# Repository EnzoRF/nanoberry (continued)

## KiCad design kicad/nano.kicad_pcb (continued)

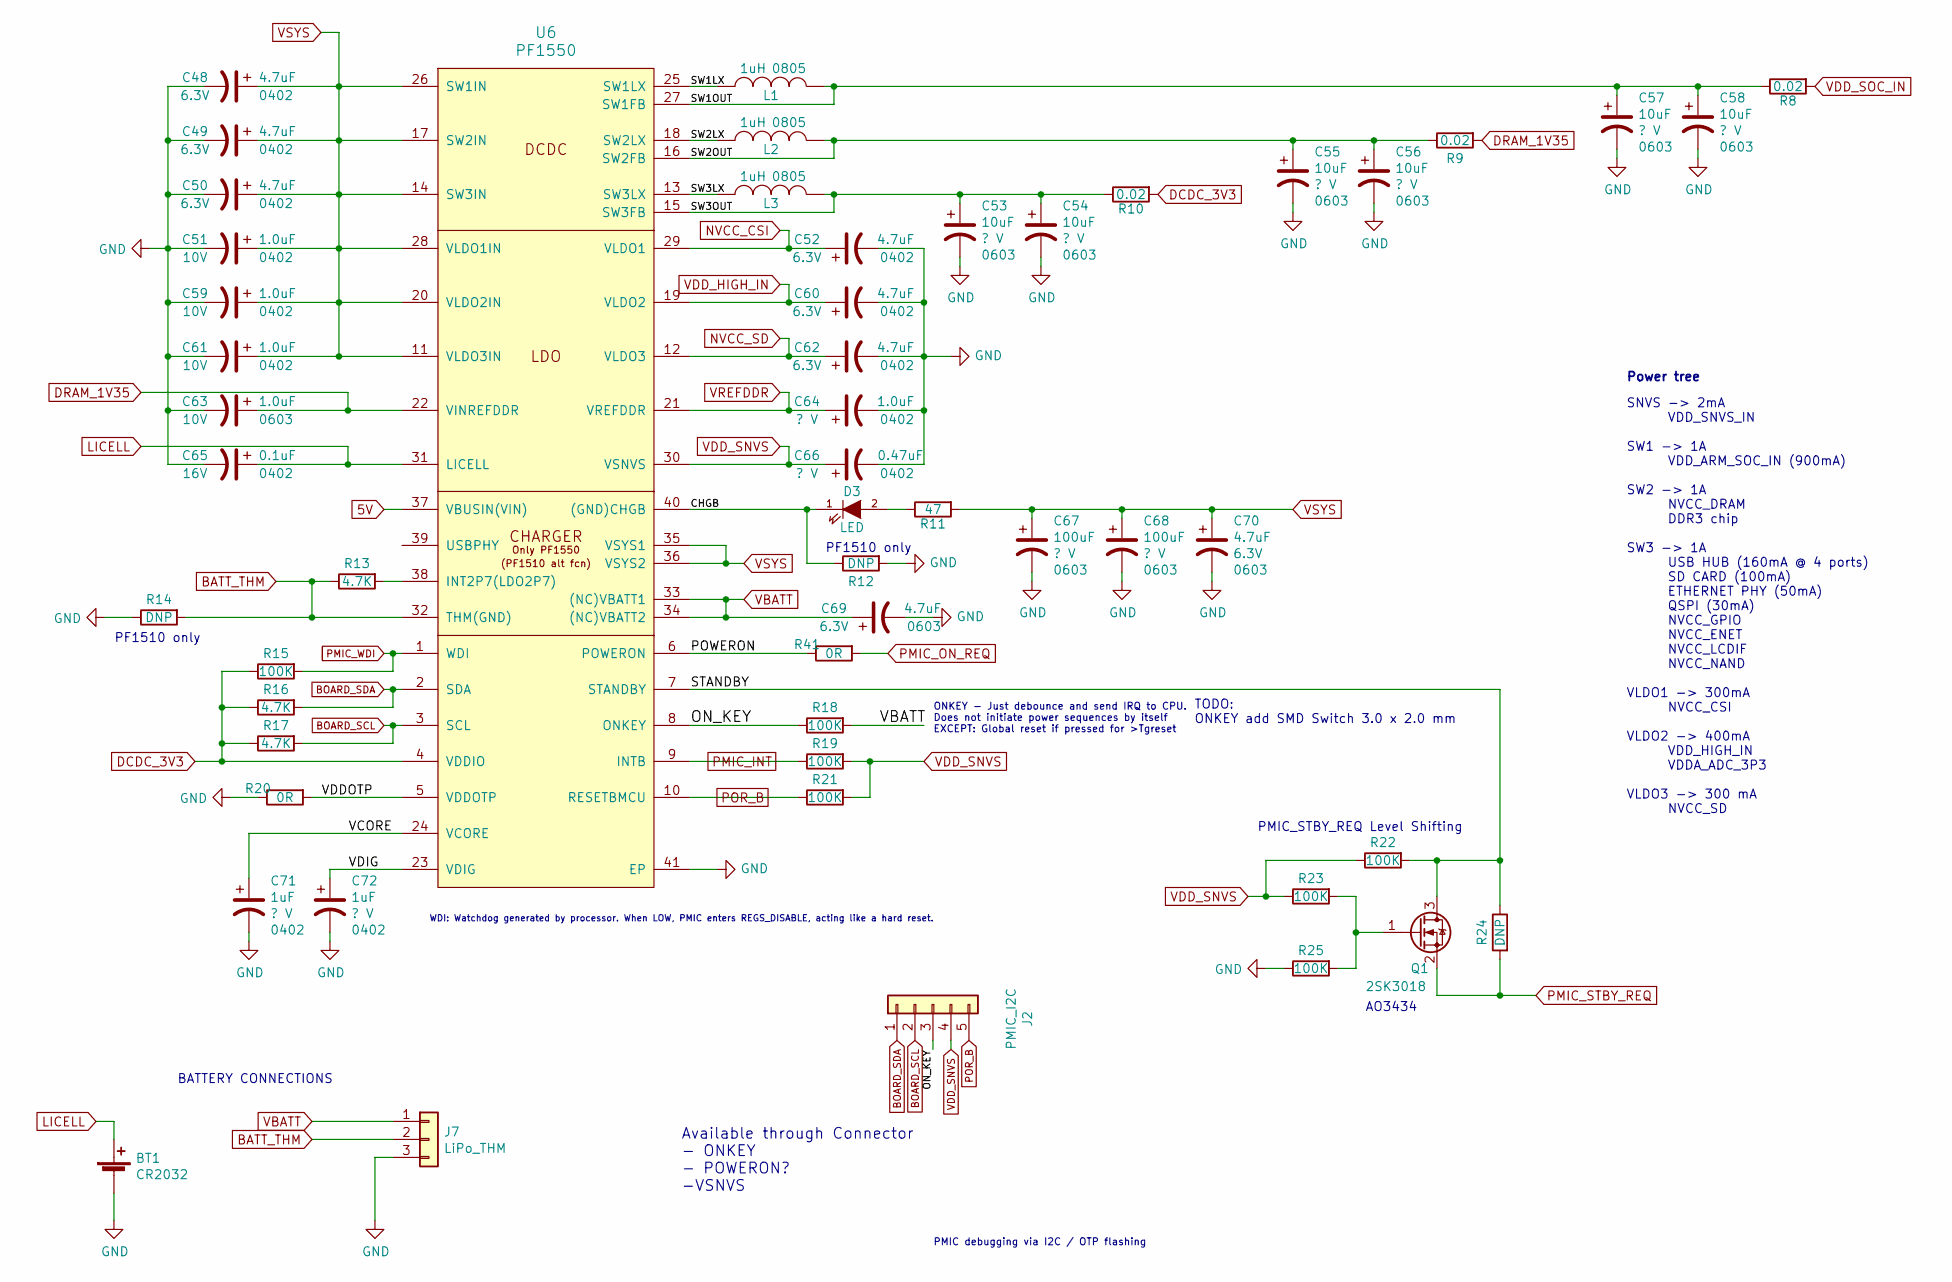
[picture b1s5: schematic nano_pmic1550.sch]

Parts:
BT1: CR2032; BatteryHolder_Keystone_1058_1x2032
C48, C49, C50, C52, C60, C62: 4.7uF; C_0402_narrow; Voltage 6.3V
C51, C59, C61: 1.0uF; C_0402_narrow; Voltage 10V
C53, C54, C55, C56, C57, C58: 10uF; C_0603_narrow; Voltage ? V
C63: 1.0uF; C_0603_narrow; Voltage 10V
C64: 1.0uF; C_0402_narrow; Voltage ? V
C65: 0.1uF; C_0603_narrow; Voltage 16V
C66: 0.47uF; C_0402_narrow; Voltage ? V
C67, C68: 100uF; C_0603_narrow; Voltage ? V
C69, C70: 4.7uF; C_0603_narrow; Voltage 6.3V
C71, C72: 1uF; C_0402_narrow; Voltage ? V
D3: LED; LED_0402_1005Metric
J2: PMIC_I2C; PinHeader_1x05_P2.54mm_Vertical
J7: LiPo_THM; PinHeader_1x03_P2.54mm_Vertical
L1, L2, L3: 1uH; L_0805_narrow
Q1: 2SK3018; SOT-23
R8, R9, R10: 0.02; R_0402_narrow
R11: 47; R_0402_narrow
R12, R14, R24: DNP; R_0402_narrow
R13, R16, R17: 4.7K; R_0402_narrow
R15, R18, R19, R21, R22, R23, R25: 100K; R_0402_narrow
R20, R41: 0R; R_0402_narrow
U6: PF1550; QFN-40-1EP_5x5mm_P0.4mm_EP3.6x3.6mm_ThermalVias

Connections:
5V: U6.37 (VBUSIN(VIN)); also elsewhere on the board
/PMIC PF1550/CHGB: D3.1 (K), R12.1, U6.40 ((GND)CHGB)
/PMIC PF1550/ON_KEY: J2.3, R18.1, U6.8 (ONKEY)
/PMIC PF1550/POWERON: R41.1, U6.6 (POWERON)
/PMIC PF1550/STANDBY: Q1.3 (D), R22.2, R24.1, U6.7 (STANDBY)
/PMIC PF1550/SW1LX: L1.2, U6.25 (SW1LX)
/PMIC PF1550/SW1OUT: C57.1, C58.1, L1.1, R8.1, U6.27 (SW1FB)
/PMIC PF1550/SW2LX: L2.2, U6.18 (SW2LX)
/PMIC PF1550/SW2OUT: C55.1, C56.1, L2.1, R9.1, U6.16 (SW2FB)
/PMIC PF1550/SW3LX: L3.2, U6.13 (SW3LX)
/PMIC PF1550/SW3OUT: C53.1, C54.1, L3.1, R10.1, U6.15 (SW3FB)
/PMIC PF1550/VCORE: C71.1, U6.24 (VCORE)
/PMIC PF1550/VDDOTP: R20.2, U6.5 (VDDOTP)
/PMIC PF1550/VDIG: C72.1, U6.23 (VDIG)
BATT_THM: J7.2, R13.1, R14.2, U6.32 (THM(GND))
BOARD_SCL: J2.2, R17.2, U6.3 (SCL); also elsewhere on the board
BOARD_SDA: J2.1, R16.2, U6.2 (SDA); also elsewhere on the board
DCDC_3V3: R10.2, R15.1, R16.1, R17.1, U6.4 (VDDIO); also elsewhere on the board
DRAM_1V35: C63.1, R9.2, U6.22 (VINREFDDR); also elsewhere on the board
GND: BT1.2 (-), C48.2, C49.2, C50.2, C51.2, C52.2, C53.2, C54.2, C55.2, C56.2, C57.2, C58.2, C59.2, C60.2, C61.2, C62.2, C63.2, C64.2, C65.2, C66.2, C67.2, C68.2, C69.2, C70.2, C71.2, C72.2, J7.3, R12.2, R14.1, R20.1, R25.1, U6.41 (EP); also elsewhere on the board
LICELL: BT1.1 (+), C65.1, U6.31 (LICELL)
NVCC_CSI: C52.1, U6.29 (VLDO1); also elsewhere on the board
NVCC_SD: C62.1, U6.12 (VLDO3); also elsewhere on the board
unnamed: D3.2 (A), R11.1
unnamed: Q1.1 (G), R23.2, R25.2
unnamed: R13.2, U6.38 (INT2P7(LDO2P7))
PMIC_INT: R19.1, U6.9 (INTB); also elsewhere on the board
PMIC_ON_REQ: R41.2; also elsewhere on the board
PMIC_STBY_REQ: Q1.2 (S), R24.2; also elsewhere on the board
PMIC_WDI: R15.2, U6.1 (WDI); also elsewhere on the board
POR_B: J2.5, R21.1, U6.10 (RESETBMCU); also elsewhere on the board
VBATT: C69.1, J7.1, R18.2, U6.33 ((NC)VBATT1), U6.34 ((NC)VBATT2); also elsewhere on the board
VDD_HIGH_IN: C60.1, U6.19 (VLDO2); also elsewhere on the board
VDD_SNVS: C66.1, J2.4, R19.2, R21.2, R22.1, R23.1, U6.30 (VSNVS); also elsewhere on the board
VDD_SOC_IN: R8.2; also elsewhere on the board
VREFDDR: C64.1, U6.21 (VREFDDR); also elsewhere on the board
VSYS: C48.1, C49.1, C50.1, C51.1, C59.1, C61.1, C67.1, C68.1, C70.1, R11.2, U6.11 (VLDO3IN), U6.14 (SW3IN), U6.17 (SW2IN), U6.20 (VLDO2IN), U6.26 (SW1IN), U6.28 (VLDO1IN), U6.35 (VSYS1), U6.36 (VSYS2)

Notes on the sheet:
Available through Connector - ONKEY - POWERON? -VSNVS
Power tree
SNVS -> 2mA VDD_SNVS_IN SW1 -> 1A VDD_ARM_SOC_IN (900mA) SW2 -> 1A NVCC_DRAM DDR3 chip SW3 -> 1A USB HUB (160mA @ 4 ports) SD CARD (100mA) ETHERNET PHY (50mA) QSPI (30mA) NVCC_GPIO NVCC_ENET NVCC_LCDIF NVCC_NAND VLDO1 -> 300mA NVCC_CSI VLDO2 -> 400mA VDD_HIGH_IN VDDA_ADC_3P3 VLDO3 -> 300 mA NVCC_SD
PF1510 only
PMIC debugging via I2C / OTP flashing
ONKEY - Just debounce and send IRQ to CPU. Does not initiate power sequences by itself EXCEPT: Global reset if pressed for >Tgreset
PMIC_STBY_REQ Level Shifting
AO3434
BATTERY CONNECTIONS
WDI: Watchdog generated by processor. When LOW, PMIC enters REGS_DISABLE, acting like a hard reset.
TODO: ONKEY add SMD Switch 3.0 x 2.0 mm

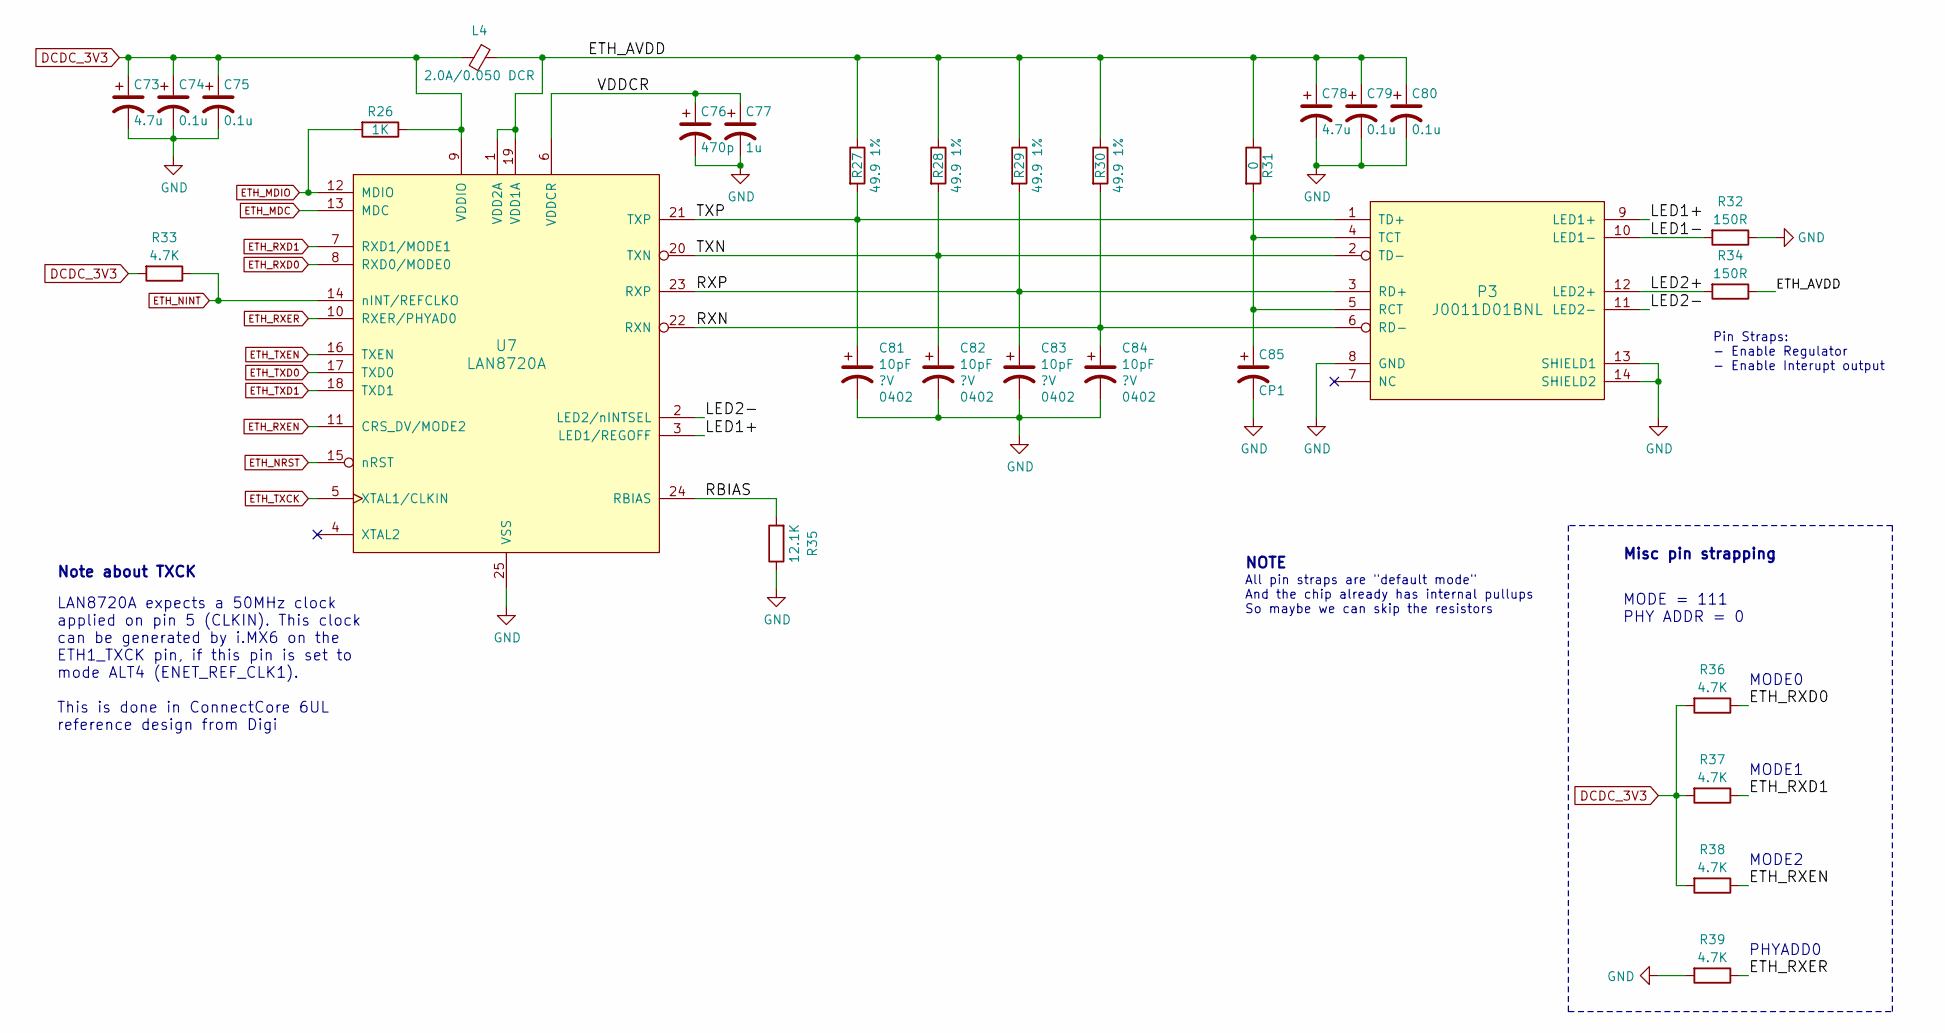
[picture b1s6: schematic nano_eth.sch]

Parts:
C73, C78: 4.7u; C_0603_narrow
C74, C75, C79, C80: 0.1u; C_0402_narrow
C76: 470p; C_0402_narrow
C77: 1u; C_0603_narrow
C81, C82, C83, C84: 10pF; C_0402_narrow; Voltage ?V
C85: CP1; C_0402_narrow
L4: 2.0A/0.050 DCR; R_0805_2012Metric
P3: J0011D01BNL; MTJ-88TX1-FSD-D1LH-M4Y
R26: 1K; R_0402_narrow
R27, R28, R29, R30: 49.9 1%; R_0402_narrow
R31: 0; R_0402_narrow
R32, R34: 150R; R_0402_narrow
R33, R36, R37, R38, R39: 4.7K; R_0402_narrow
R35: 12.1K; R_0402_narrow
U7: LAN8720A; QFN-24-1EP_4x4mm_P0.5mm_EP2.6x2.6mm_ThermalVias

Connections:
/ETHERNET/ETH_AVDD: C78.1, C79.1, C80.1, L4.1, R27.1, R28.1, R29.1, R30.1, R31.1, R34.1, U7.1 (VDD2A), U7.19 (VDD1A)
/ETHERNET/LED1+: P3.9 (LED1+), U7.3 (LED1/REGOFF)
/ETHERNET/LED1-: P3.10 (LED1-), R32.2
/ETHERNET/LED2+: P3.12 (LED2+), R34.2
/ETHERNET/LED2-: P3.11 (LED2-), U7.2 (LED2/nINTSEL)
/ETHERNET/RBIAS: R35.2, U7.24 (RBIAS)
/ETHERNET/RXN: C84.1, P3.6 (RD-), R30.2, U7.22 (RXN)
/ETHERNET/RXP: C83.1, P3.3 (RD+), R29.2, U7.23 (RXP)
/ETHERNET/TXN: C82.1, P3.2 (TD-), R28.2, U7.20 (TXN)
/ETHERNET/TXP: C81.1, P3.1 (TD+), R27.2, U7.21 (TXP)
/ETHERNET/VDDCR: C76.1, C77.1, U7.6 (VDDCR)
DCDC_3V3: C73.1, C74.1, C75.1, L4.2, R26.1, R33.2, R36.2, R37.2, R38.2, U7.9 (VDDIO); also elsewhere on the board
ETH_MDC: U7.13 (MDC); also elsewhere on the board
ETH_MDIO: R26.2, U7.12 (MDIO); also elsewhere on the board
ETH_NINT: R33.1, U7.14 (nINT/REFCLKO); also elsewhere on the board
ETH_NRST: U7.15 (nRST); also elsewhere on the board
ETH_RXD0: R36.1, U7.8 (RXD0/MODE0); also elsewhere on the board
ETH_RXD1: R37.1, U7.7 (RXD1/MODE1); also elsewhere on the board
ETH_RXEN: R38.1, U7.11 (CRS_DV/MODE2); also elsewhere on the board
ETH_RXER: R39.1, U7.10 (RXER/PHYAD0); also elsewhere on the board
ETH_TXCK: U7.5 (XTAL1/CLKIN); also elsewhere on the board
ETH_TXD0: U7.17 (TXD0); also elsewhere on the board
ETH_TXD1: U7.18 (TXD1); also elsewhere on the board
ETH_TXEN: U7.16 (TXEN); also elsewhere on the board
GND: C73.2, C74.2, C75.2, C76.2, C77.2, C78.2, C79.2, C80.2, C81.2, C82.2, C83.2, C84.2, C85.2, P3.8 (GND), P3.13 (SHIELD1), P3.14 (SHIELD2), R32.1, R35.1, R39.2, U7.25 (VSS); also elsewhere on the board
unnamed: C85.1, P3.4 (TCT), P3.5 (RCT), R31.2

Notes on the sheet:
Note about TXCK
LAN8720A expects a 50MHz clock applied on pin 5 (CLKIN). This clock can be generated by i.MX6 on the ETH1_TXCK pin, if this pin is set to mode ALT4 (ENET_REF_CLK1). This is done in ConnectCore 6UL reference design from Digi
PHYADD0
MODE0
MODE1
MODE2
MODE = 111 PHY ADDR = 0
Misc pin strapping
Pin Straps: - Enable Regulator - Enable Interupt output
NOTE
All pin straps are "default mode" And the chip already has internal pullups So maybe we can skip the resistors

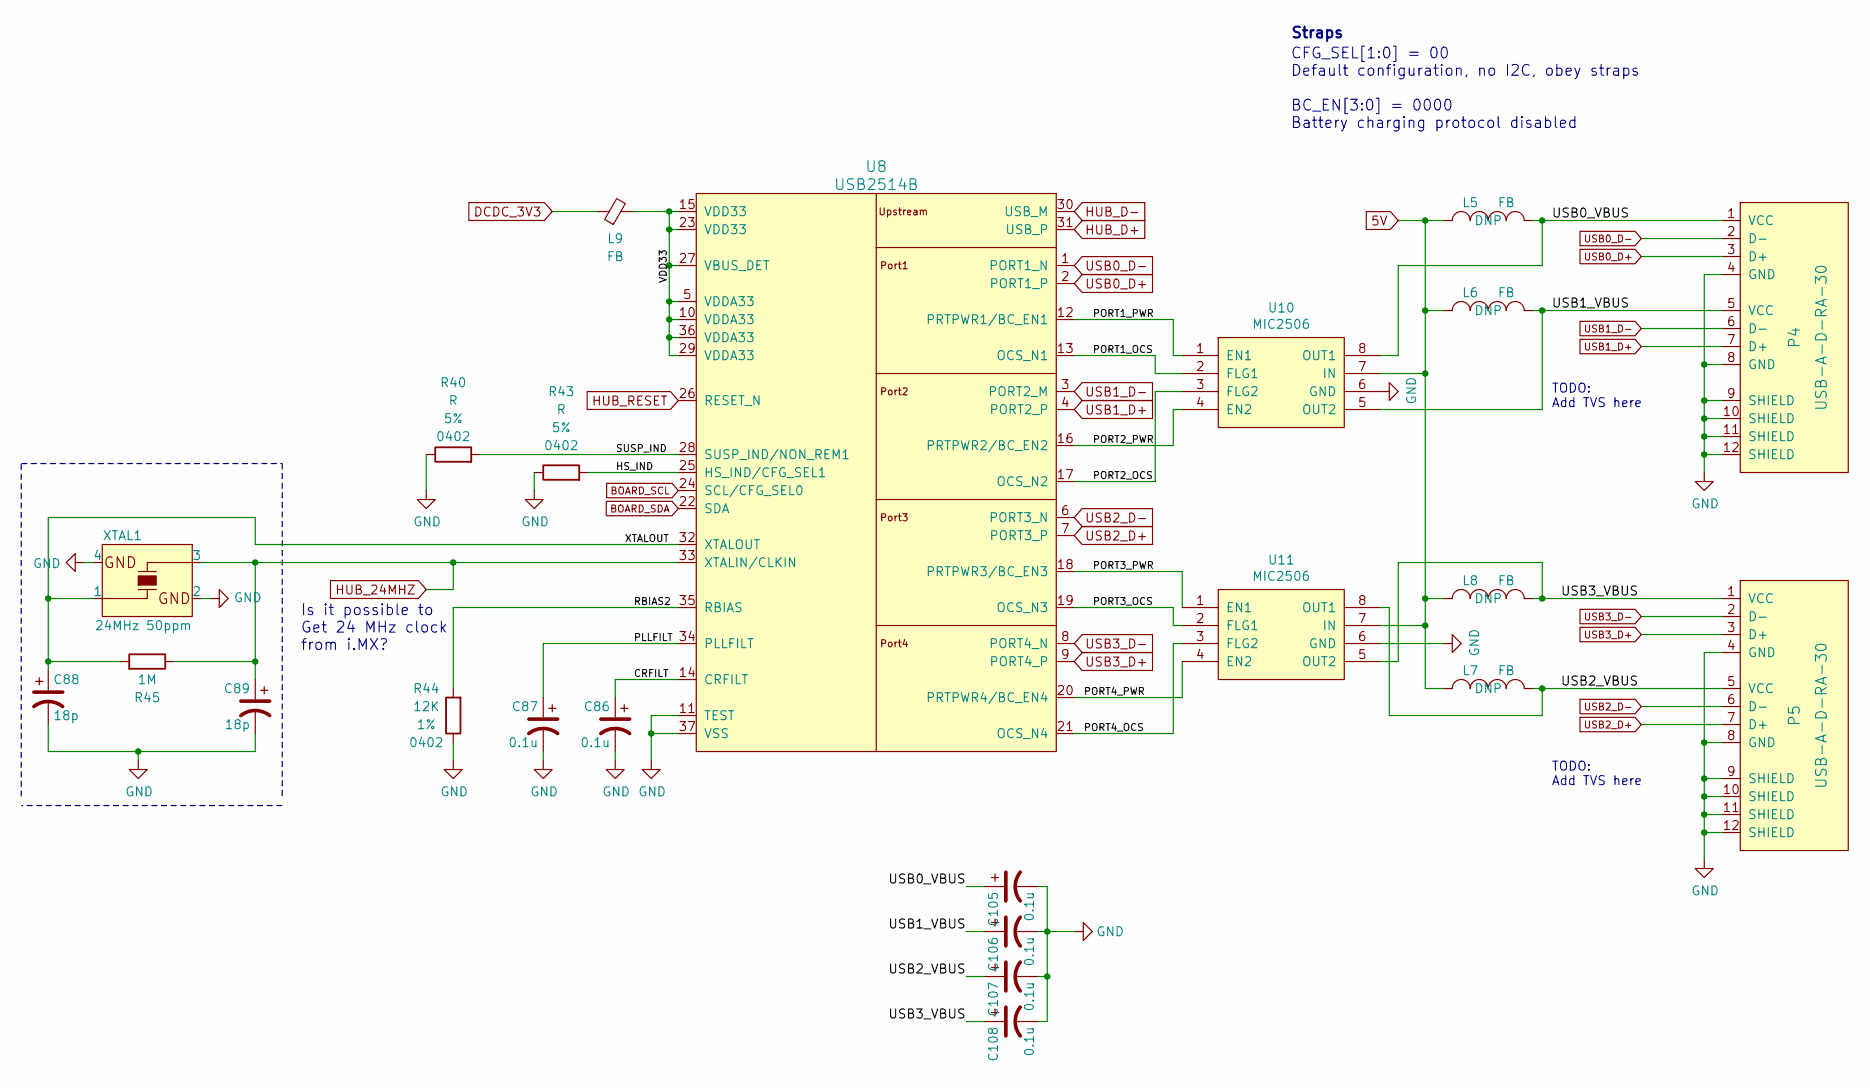
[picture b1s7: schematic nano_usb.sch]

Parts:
C86, C87, C105, C106, C107, C108: 0.1u; C_0402_narrow
C88, C89: 18p; C_0402_narrow
L5, L6, L7, L8, L9: FB; L_0805_narrow
P4, P5: USB-A-D-RA-30
R40, R43: R; R_0402_narrow; Tolerance 5%
R44: 12K; R_0402_narrow; Tolerance 1%
R45: 1M; R_0402_narrow
U8: USB2514B; QFN-36-1EP_6x6mm_P0.5mm_EP3.7x3.7mm_ThermalVias
U10, U11: MIC2506; SOIC-8_3.9x4.9mm_P1.27mm
XTAL1: 24MHz 50ppm; Oscillator_SMD_EuroQuartz_XO32-4Pin_3.2x2.5mm

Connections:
5V: L5.1, L6.1, L7.1, L8.1, U10.7 (IN), U11.7 (IN); also elsewhere on the board
/USB HUB/CRFILT: C86.1, U8.14 (CRFILT)
/USB HUB/HS_IND: R43.2, U8.25 (HS_IND/CFG_SEL1)
/USB HUB/PLLFILT: C87.1, U8.34 (PLLFILT)
/USB HUB/PORT1_OCS: U8.13 (OCS_N1), U10.2 (FLG1)
/USB HUB/PORT1_PWR: U8.12 (PRTPWR1/BC_EN1), U10.1 (EN1)
/USB HUB/PORT2_OCS: U8.17 (OCS_N2), U10.3 (FLG2)
/USB HUB/PORT2_PWR: U8.16 (PRTPWR2/BC_EN2), U10.4 (EN2)
/USB HUB/PORT3_OCS: U8.19 (OCS_N3), U11.2 (FLG1)
/USB HUB/PORT3_PWR: U8.18 (PRTPWR3/BC_EN3), U11.1 (EN1)
/USB HUB/PORT4_OCS: U8.21 (OCS_N4), U11.3 (FLG2)
/USB HUB/PORT4_PWR: U8.20 (PRTPWR4/BC_EN4), U11.4 (EN2)
/USB HUB/RBIAS2: R44.2, U8.35 (RBIAS)
/USB HUB/SUSP_IND: R40.2, U8.28 (SUSP_IND/NON_REM1)
/USB HUB/USB0_VBUS: C105.1, L5.2, P4.1 (VCC), U10.8 (OUT1)
/USB HUB/USB1_VBUS: C106.1, L6.2, P4.5 (VCC), U10.5 (OUT2)
/USB HUB/USB2_VBUS: C107.1, L7.2, P5.5 (VCC), U11.8 (OUT1)
/USB HUB/USB3_VBUS: C108.1, L8.2, P5.1 (VCC), U11.5 (OUT2)
/USB HUB/VDD33: L9.2, U8.5 (VDDA33), U8.10 (VDDA33), U8.15 (VDD33), U8.23 (VDD33), U8.27 (VBUS_DET), U8.29 (VDDA33), U8.36 (VDDA33)
/USB HUB/XTALOUT: C88.1, R45.2, U8.32 (XTALOUT), XTAL1.1
BOARD_SCL: U8.24 (SCL/CFG_SEL0); also elsewhere on the board
BOARD_SDA: U8.22 (SDA); also elsewhere on the board
DCDC_3V3: L9.1; also elsewhere on the board
GND: C86.2, C87.2, C88.2, C89.2, C105.2, C106.2, C107.2, C108.2, P4.4 (GND), P4.8 (GND), P4.9 (SHIELD), P4.10 (SHIELD), P4.11 (SHIELD), P4.12 (SHIELD), P5.4 (GND), P5.8 (GND), P5.9 (SHIELD), P5.10 (SHIELD), P5.11 (SHIELD), P5.12 (SHIELD), R40.1, R43.1, R44.1, U8.11 (TEST), U8.37 (VSS), U10.6 (GND), U11.6 (GND), XTAL1.2, XTAL1.4; also elsewhere on the board
HUB_24MHZ: C89.1, R45.1, U8.33 (XTALIN/CLKIN), XTAL1.3; also elsewhere on the board
HUB_D+: U8.31 (USB_P); also elsewhere on the board
HUB_D-: U8.30 (USB_M); also elsewhere on the board
HUB_RESET: U8.26 (RESET_N); also elsewhere on the board
USB0_D+: P4.3 (D+), U8.2 (PORT1_P)
USB0_D-: P4.2 (D-), U8.1 (PORT1_N)
USB1_D+: P4.7 (D+), U8.4 (PORT2_P)
USB1_D-: P4.6 (D-), U8.3 (PORT2_M)
USB2_D+: P5.7 (D+), U8.7 (PORT3_P)
USB2_D-: P5.6 (D-), U8.6 (PORT3_N)
USB3_D+: P5.3 (D+), U8.9 (PORT4_P)
USB3_D-: P5.2 (D-), U8.8 (PORT4_N)

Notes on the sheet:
Is it possible to Get 24 MHz clock from i.MX?
Straps
CFG_SEL[1:0] = 00 Default configuration, no I2C, obey straps BC_EN[3:0] = 0000 Battery charging protocol disabled
TODO: Add TVS here

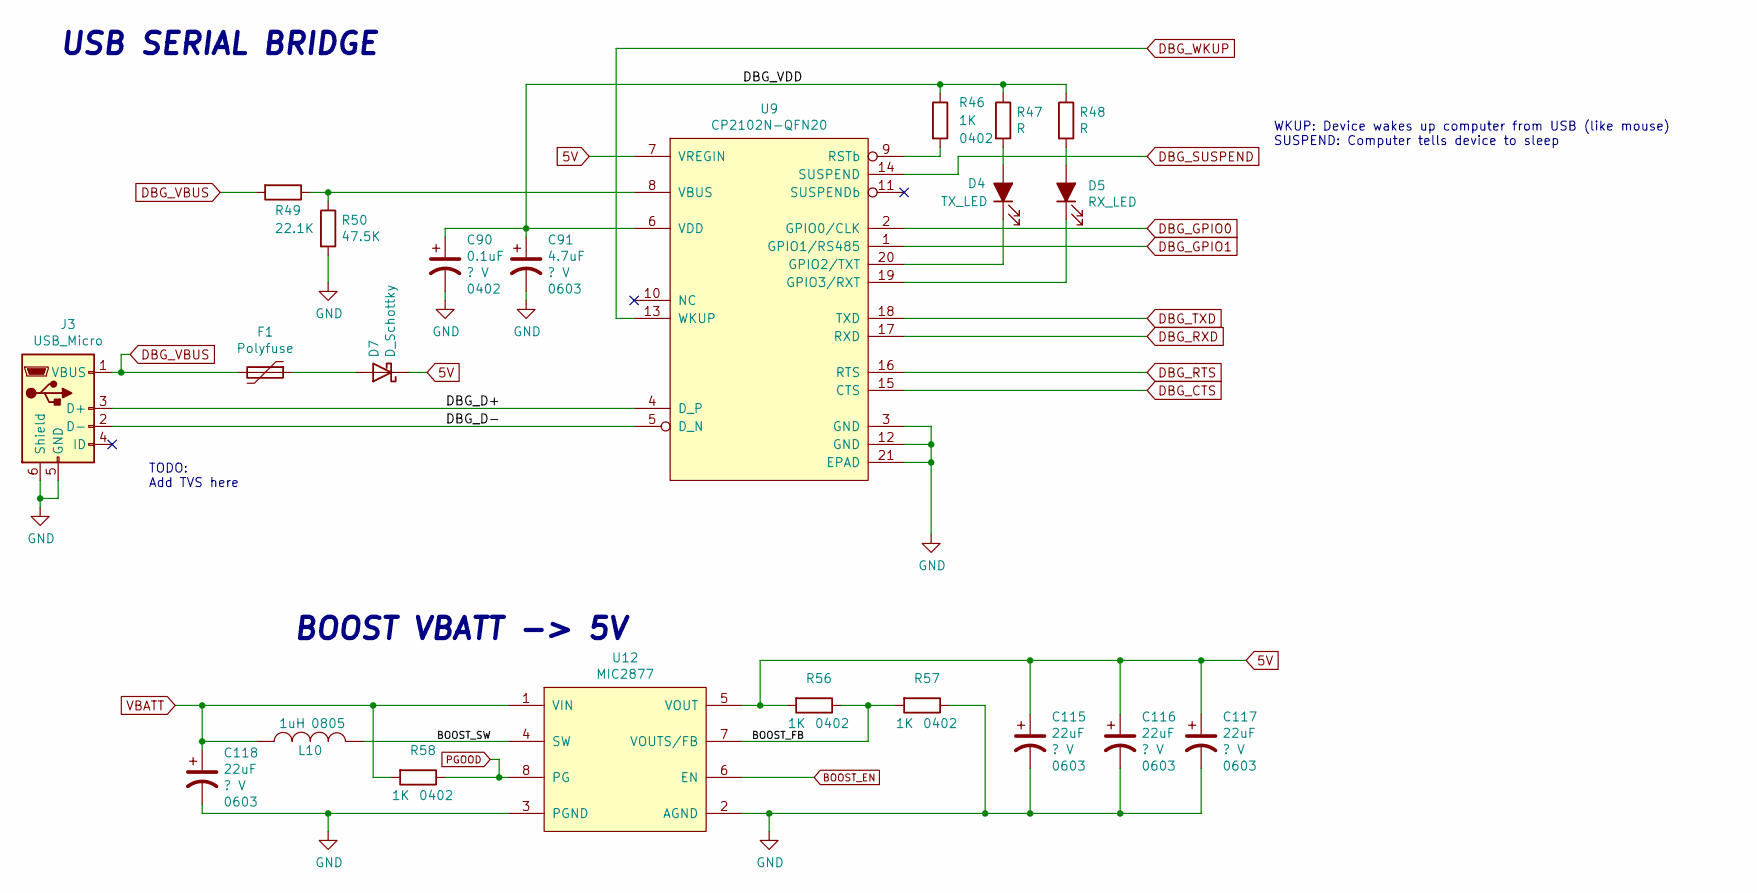
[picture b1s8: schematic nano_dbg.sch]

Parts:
C90: 0.1uF; C_0402_narrow; Voltage ? V
C91: 4.7uF; C_0603_narrow; Voltage ? V
C115, C116, C117, C118: 22uF; C_0603_narrow; Voltage ? V
D4: TX_LED; LED_0402_1005Metric
D5: RX_LED; LED_0402_1005Metric
D7: D_Schottky; D_0805_2012Metric
F1: Polyfuse; D_0805_2012Metric
J3: USB_Micro; MCR-B-S-RA-SMT-CS5
L10: 1uH; L_Bourns-SRN4018
R46, R56, R57, R58: 1K; R_0402_narrow
R47, R48: R; R_0402_narrow
R49: 22.1K; R_0402_narrow
R50: 47.5K; R_0402_narrow
U9: CP2102N-QFN20; SiliconLabs_QFN-20-1EP_3x3mm_CUSTOM
U12: MIC2877

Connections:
5V: C115.1, C116.1, C117.1, D7.1 (K), R56.2, U9.7 (VREGIN), U12.5 (VOUT); also elsewhere on the board
/USB DEBUG & OTG/BOOST_FB: R56.1, R57.2, U12.7 (VOUTS/FB)
/USB DEBUG & OTG/BOOST_SW: L10.1, U12.4 (SW)
/USB DEBUG & OTG/DBG_D+: J3.3 (D+), U9.4 (D_P)
/USB DEBUG & OTG/DBG_D-: J3.2 (D-), U9.5 (D_N)
/USB DEBUG & OTG/DBG_VDD: C90.1, C91.1, R46.1, R47.1, R48.1, U9.6 (VDD)
BOOST_EN: U12.6 (EN)
DBG_CTS: U9.15 (CTS); also elsewhere on the board
DBG_GPIO0: U9.2 (GPIO0/CLK); also elsewhere on the board
DBG_GPIO1: U9.1 (GPIO1/RS485); also elsewhere on the board
DBG_RTS: U9.16 (RTS); also elsewhere on the board
DBG_RXD: U9.17 (RXD); also elsewhere on the board
DBG_SUSPEND: U9.14 (SUSPEND); also elsewhere on the board
DBG_TXD: U9.18 (TXD); also elsewhere on the board
DBG_VBUS: F1.2, J3.1 (VBUS), R49.2
DBG_WKUP: U9.13 (WKUP); also elsewhere on the board
GND: C90.2, C91.2, C115.2, C116.2, C117.2, C118.2, J3.5 (GND), J3.6 (Shield), R50.2, R57.1, U9.3 (GND), U9.12 (GND), U9.21 (EPAD), U12.2 (AGND), U12.3 (PGND); also elsewhere on the board
unnamed: D4.1 (K), U9.20 (GPIO2/TXT)
unnamed: D4.2 (A), R47.2
unnamed: D5.1 (K), U9.19 (GPIO3/RXT)
unnamed: D5.2 (A), R48.2
unnamed: D7.2 (A), F1.1
unnamed: R46.2, U9.9 (RSTb)
unnamed: R49.1, R50.1, U9.8 (VBUS)
PGOOD: R58.1, U12.8 (PG)
VBATT: C118.1, L10.2, R58.2, U12.1 (VIN); also elsewhere on the board

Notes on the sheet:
WKUP: Device wakes up computer from USB (like mouse) SUSPEND: Computer tells device to sleep
TODO: Add TVS here
USB SERIAL BRIDGE
BOOST VBATT -> 5V

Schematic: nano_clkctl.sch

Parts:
C96, C97: 18p; C_0402_narrow
C98, C99: 18pF; C_0402_narrow; Voltage ?
C100: 0.1uF; C_0402_narrow; Voltage 25V
C101: 1.0uF; C_0402_narrow; Voltage 10V
FB1: Bead; R_0402_narrow
J5: JTAG; PinHeader_2x05_P1.00mm_Vertical_SMD
R52: 4.7k; R_0402_narrow
R53: 1M; R_0402_narrow; Tolerance ?
R54: 499; R_0402_narrow
R55: 2.2M; R_0402_narrow
SB1, SB2, SB3, SB4: 4.7K; R_0402_narrow; Tolerance ?
U1: IMX6UL_BGA289
XTAL2: 24MHz 50ppm; Oscillator_SMD_EuroQuartz_XO32-4Pin_3.2x2.5mm
Y1: 32.768 kHz; Crystal_SMD_3215-2Pin_3.2x1.5mm

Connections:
/Clock_and_Control/BOOT0: SB3.1, SB4.1, U1.T10 (BOOT_MODE0)
/Clock_and_Control/BOOT1: SB1.1, SB2.1, U1.U10 (BOOT_MODE1)
/Clock_and_Control/IMX_XTALI: C99.1, R53.1, R55.1, U1.T16 (XTALI), XTAL2.3
/Clock_and_Control/IMX_XTALO: C98.1, R53.2, R54.1, U1.T17 (XTALO), XTAL2.1
/Clock_and_Control/JTAG_MOD: R52.2, U1.P15 (JTAG_MOD)
/Clock_and_Control/JTAG_TCK: J5.4, U1.M14 (JTAG_TCK)
/Clock_and_Control/JTAG_TDI: J5.8, U1.N16 (JTAG_TDI)
/Clock_and_Control/JTAG_TDO: J5.6, U1.N15 (JTAG_TDO)
/Clock_and_Control/JTAG_TMS: J5.2, U1.P14 (JTAG_TMS)
/Clock_and_Control/JTAG_TRST_B: J5.7, U1.N14 (JTAG_TRST_B)
/Clock_and_Control/RTC_XTALI: C97.1, U1.T11 (RTC_XTALI), Y1.2
/Clock_and_Control/RTC_XTALO: C96.1, U1.U11 (RTC_XTALO), Y1.1
/Clock_and_Control/SNVS8: U1.N9 (SNVS_TAMPER8)
/Clock_and_Control/VDDA_ADC: C100.1, C101.1, FB1.2, U1.L13 (VDDA_ADC_3P3), U1.M13 (ADC_VREFH)
A71_NRST: U1.N8 (SNVS_TAMPER5); also elsewhere on the board
DCDC_3V3: J5.1; also elsewhere on the board
GND: C96.2, C97.2, C98.2, C99.2, C100.2, C101.2, J5.3, J5.5, J5.9, R52.1, R54.2, R55.2, SB2.2, SB4.2, U1.N7 (TEST_MODE), XTAL2.2, XTAL2.4; also elsewhere on the board
HUB_RESET: U1.N11 (SNVS_TAMPER6); also elsewhere on the board
PMIC_INT: U1.P11 (SNVS_TAMPER2); also elsewhere on the board
PMIC_ON_REQ: U1.T9 (SNVS_PMIC_ON_REQ); also elsewhere on the board
PMIC_STBY_REQ: U1.U9 (CCM_PMIC_STBY_REQ); also elsewhere on the board
PMIC_WDI: U1.N10 (SNVS_TAMPER7); also elsewhere on the board
POR_B: J5.10, U1.P8 (POR_B); also elsewhere on the board
SNVS0: U1.R10 (SNVS_TAMPER0); also elsewhere on the board
SNVS1: U1.R9 (SNVS_TAMPER1); also elsewhere on the board
SNVS3: U1.P10 (SNVS_TAMPER3); also elsewhere on the board
SNVS4: U1.P9 (SNVS_TAMPER4); also elsewhere on the board
VDD_HIGH_IN: FB1.1; also elsewhere on the board
VDD_SNVS: SB1.2, SB3.2; also elsewhere on the board

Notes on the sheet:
ONOFF - Not connected (controlled by PMIC) IMX6ULLRM Fig.51-2
POR_B - Open drain input controlled by PMIC
TRST is not used in std JTAG conn Standard use is key (missing pin)
No place on PCB
BOOT1 BOOT0 ------------ 0 0 0 1 1 0 1 1

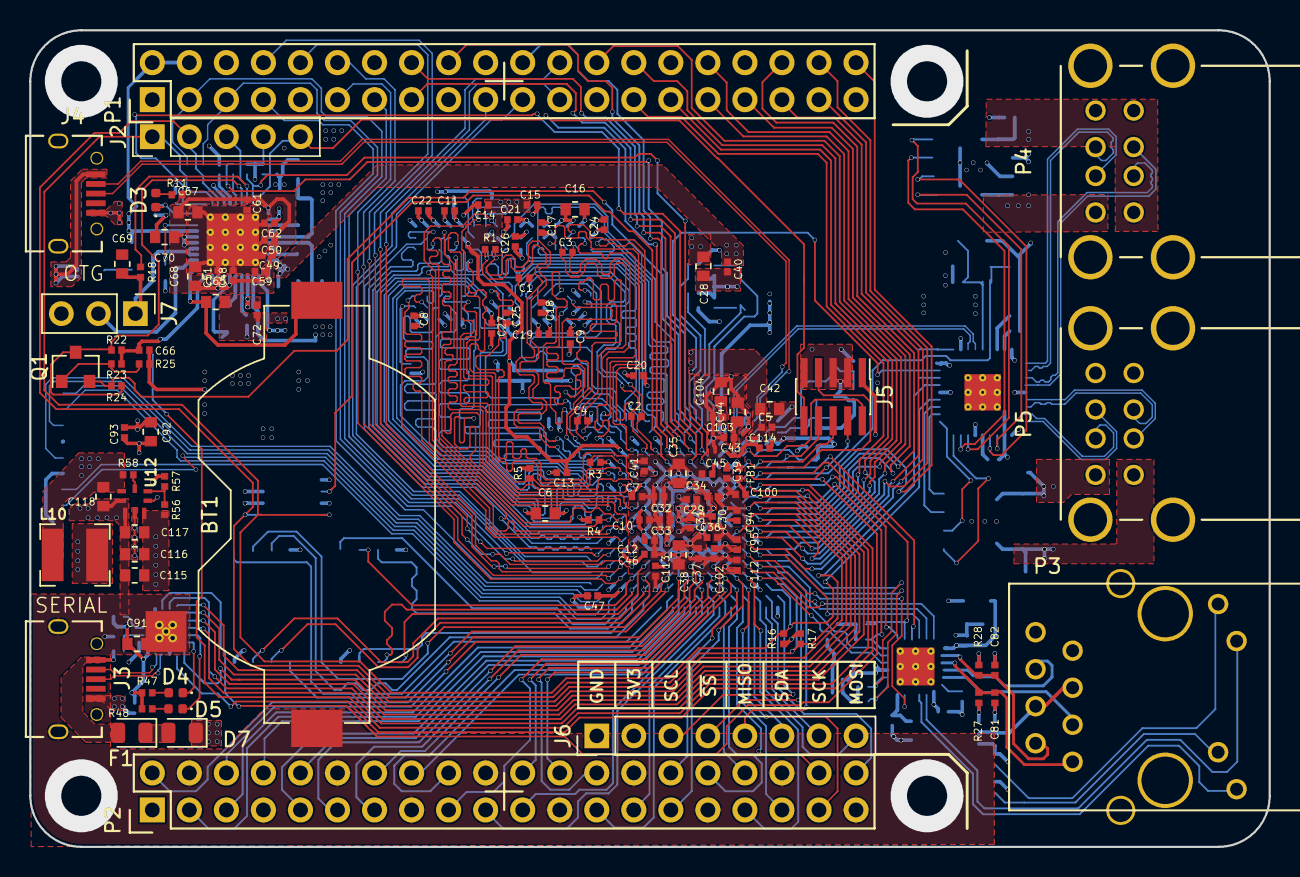
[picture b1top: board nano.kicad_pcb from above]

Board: 4 copper layers, 85.0 x 56.0 mm, 229 parts (0 on the bottom side), 276 nets.

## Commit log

2020-04-09 Add README
2020-05-19 Move xtal
2020-05-19 uart2/3 layout
2020-05-19 layout: move jtag connector
2020-05-24 layout: move usb hub, improve gpio connections
2020-05-25 fix DRC
2020-05-25 add block diagram
2020-06-11 layout improvement
2020-06-12 add i2c for ULZ
2020-06-12 pmic_int connection
2020-06-12 remove vsnvs diodes
